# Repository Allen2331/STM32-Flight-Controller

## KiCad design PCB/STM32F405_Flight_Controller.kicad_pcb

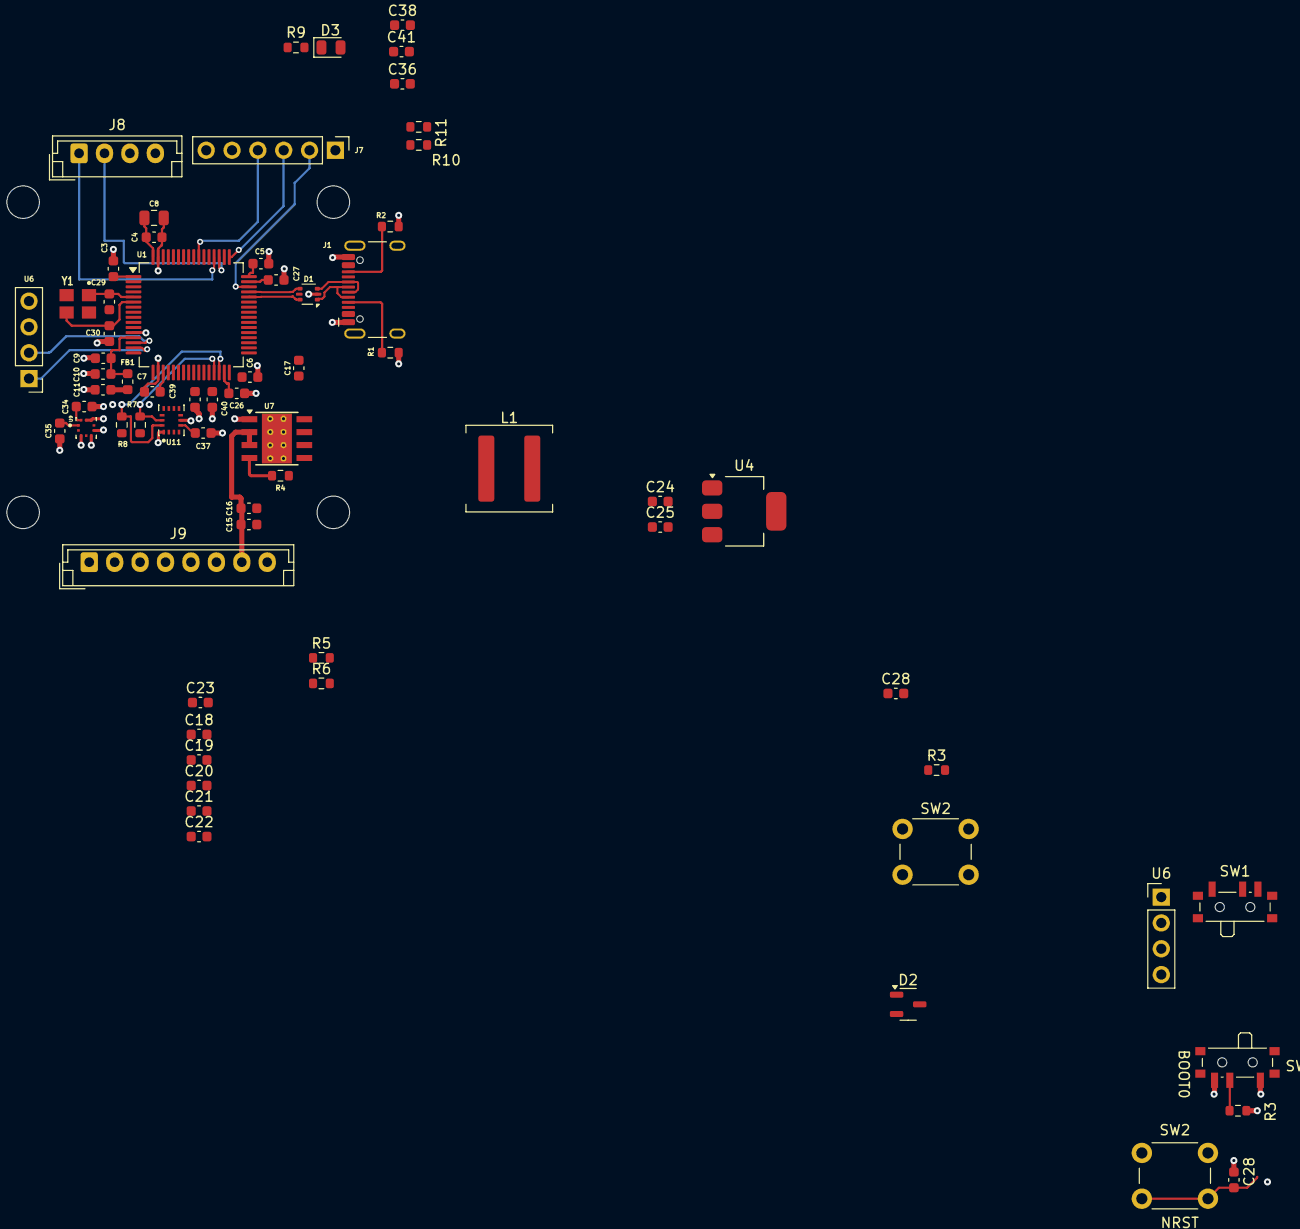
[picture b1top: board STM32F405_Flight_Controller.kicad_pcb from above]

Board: 4 copper layers, 71 parts (0 on the bottom side), 39 nets.

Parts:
C3, C4, C5, C6, C7, C18, C28, C28#2, C34, C35, C38, C41: 100nF; C_0603_1608Metric
C8: 10uF; C_0805_2012Metric
C9, C37: 10nF; C_0603_1608Metric
C10, C11, C17, C36: 1uF; C_0603_1608Metric
C15: 10uF; C_0603_1608Metric
C16: 220nF; C_0603_1608Metric
C19: 39pF; C_0603_1608Metric
C20, C21, C22, C23: 22uF; C_0603_1608Metric
C24, C25: 4.7uF; C_0603_1608Metric
C26, C27: 2.2uF; C_0603_1608Metric
C29, C30: 15pF; C_0603_1608Metric
C39: 0.1u; C_0603_1608Metric
C40: 2.2u; C_0603_1608Metric
D1: USBLC6-2P6; SOT-666
D2: BAT54C; SOT-23-3
D3: LED; LED_0805_2012Metric
FB1: FerriteBead; L_0603_1608Metric
H1, H2, H3, H4: MountingHole; MountingHole_3.2mm_M3_ISO7380
J1: USB_C_Receptacle_USB2.0_16P; USB_C_Receptacle_HCTL_HC-TYPE-C-16P-01A
J7: SWD; PinHeader_1x06_P2.54mm_Vertical
J8: Conn_01x04; JST_EH_B4B-EH-A_1x04_P2.50mm_Vertical
J9: Conn_01x08; JST_EH_B8B-EH-A_1x08_P2.50mm_Vertical
L1: 6.8uH; L_Coilcraft_XAL7030-682
R1, R2: 5.1K; R_0603_1608Metric
R3, R3#2, R11: 10K; R_0603_1608Metric
R4, R5: 100k; R_0603_1608Metric
R6: 24.9k; R_0603_1608Metric
R7, R8: 2.2K; R_0603_1608Metric
R9: 1K; R_0603_1608Metric
R10: 15K; R_0603_1608Metric
SW1, SW1#2: SW_SPDT; SW_SPDT_PCM12
SW2, SW2#2: SW_Push; SW_PUSH_6mm_H4.3mm
U1: STM32F405RGTx; LQFP-64_10x10mm_P0.5mm
U4: AP7361C-33E; SOT-223-3_TabPin2
U6, U6#2: PinHeader_1x04_P2.54mm_Vertical
U7: LMR33640DDDA; Texas_HSOP-8-1EP_3.9x4.9mm_P1.27mm_ThermalVias
U9: BMP390L
U11: XDCR_ICM-42670-P
Y1: 16MHz Crystal; OSC_X322516MLB4SI

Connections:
+3.3V: C3.1, C4.1, C5.1, C6.1, C7.1, C8.1, C11.1, C25.2, C34.1, C35.1, C36.1, C37.2, C38.1, C39.1, C40.1, D3.2 (A), FB1.1, J7.1, J8.3, R7.1, R8.1, SW1.1 (A), SW1#2.1 (A), U1.1 (VBAT), U1.19 (VDD), U1.32 (VDD), U1.48 (VDD), U1.64 (VDD), U4.3 (VO), U9.1 (VDDIO), U9.10 (VDD), U11.5 (VDDIO), U11.8 (VDD), U11.12 (CS)
+5V: C19.2, C20.2, C21.2, C22.2, C23.2, C24.2, D2.2 (A1), D2.3 (K), L1.2, R5.1, U4.1 (VI), U6.3 (5V), U6#2.3 (5V)
+BATT: C15.1, C16.1, J9.7, R10.1, U7.2 (VIN), U7.3 (EN)
BATT_SENSE: R10.2, R11.1, U1.9 (PC1)
BMP_INT: U1.61 (PB8), U9.7 (INT)
BOOT0: R3.2, R3#2.2, SW1.2 (B), SW1#2.2 (B), U1.60 (BOOT0)
ESC_1: J9.6, U1.26 (PB0)
ESC_2: J9.5, U1.27 (PB1)
ESC_3: J9.4, U1.38 (PC7)
ESC_4: J9.3, U1.37 (PC6)
GND: C3.2, C4.2, C5.2, C6.2, C7.2, C8.2, C9.2, C10.2, C11.2, C15.2, C16.2, C17.2, C20.1, C21.1, C22.1, C23.1, C24.1, C25.1, C26.2, C27.2, C28.1, C28#2.1, C29.1, C30.1, C34.2, C35.2, C36.2, C37.1, C38.2, C39.2, C40.2, C41.2, D1.2 (VN), J1.A1 (GND), J1.A12 (GND), J1.B1 (GND), J1.B12 (GND), J1.S1 (SHIELD), J7.6, J8.4, J9.8, R1.2, R2.2, R3.1, R3#2.1, R6.2, R9.1, R11.2, SW1.3 (C), SW1#2.3 (C), SW2.1, SW2#2.1, U1.12 (VSSA), U1.18 (VSS), U1.63 (VSS), U4.2 (GND), U6.4 (GND), U6#2.4 (GND), U7.1 (GND), U7.9 (GND), U9.3 (VSS), U9.5 (SDO), U9.6 (CSB), U9.8 (VSS), U9.9 (VSS), U11.1 (SDO), U11.6 (GND), Y1.2, Y1.4
IMU_INT: U1.33 (PB12), U11.4 (INT)
NRST: C28.2, C28#2.2, J7.5, SW2.2, SW2#2.2, U1.7 (NRST)
unnamed: D1.5 (VP), D2.1 (A2), J1.A4 (VBUS), J1.A9 (VBUS), J1.B4 (VBUS), J1.B9 (VBUS)
unnamed: D3.1 (K), R9.2
unnamed: J1.A5 (CC1), R1.1
unnamed: J1.B5 (CC2), R2.1
unnamed: C29.2, U1.5 (PH0), Y1.1
unnamed: C30.2, U1.6 (PH1), Y1.3
unnamed: C26.1, U1.31 (VCAP_1)
unnamed: C27.1, U1.47 (VCAP_2)
unnamed: C9.1, C10.1, FB1.2, U1.13 (VDDA)
unnamed: C18.1, U7.7 (BOOT)
unnamed: C19.1, R5.2, R6.1, U7.5 (FB)
unnamed: R4.1, U7.4 (PG)
unnamed: C18.2, L1.1, U7.8 (SW)
unnamed: C17.1, R4.2, U7.6 (VCC)
SCL: R7.2, U1.29 (PB10), U9.2 (SCK), U11.13 (SCL)
SDA: R8.2, U1.30 (PB11), U9.4 (SDI), U11.14 (SDA)
SWCLK: J7.3, U1.49 (PA14)
SWDIO: J7.2, U1.46 (PA13)
SWO: J7.4, U1.55 (PB3)
UART1_RX: U1.15 (PA1), U6.1 (RX), U6#2.1 (RX)
UART1_TX: U1.14 (PA0), U6.2 (TX), U6#2.2 (TX)
UART2_RX: J8.1, U1.52 (PC11)
UART2_TX: J8.2, U1.51 (PC10)
UART_ESC: J9.1, U1.54 (PD2)
USB_C_D_N: D1.1 (L1), D1.6 (L1), J1.A7 (D-), J1.B7 (D-), U1.44 (PA11)
USB_C_D_P: D1.3 (L2), D1.4 (L2), J1.A6 (D+), J1.B6 (D+), U1.45 (PA12)

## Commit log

2024-08-29 Initial commit of STM32 Flight Controller
2024-09-09 Create Schematic Folder
2024-09-09 Create PDF
2024-09-19 Add files via upload
    Updated schematic
2024-09-19 Add files via upload
    Added PCB file
2024-09-20 Add files via upload
    PNG of layers
2024-09-27 Add files via upload
    updated
2024-09-27 Create a
2024-09-27 Add files via upload
    added gerbers
2024-09-30 Add files via upload
    updated layout
2024-10-01 firmware files
2024-10-01 updated folder name
2024-10-01 folder name
2024-10-01 name
2024-10-23 Add files via upload
    pdf version of schematic
2024-10-28 created MPU6050 header
2024-11-04 added mpu6050
2024-11-04 register address
2024-11-11 added to mpu6050 header
2024-11-21 bmp280
2025-03-03 Add files via upload
    Updated schematic with new sensors
2025-03-04 Add files via upload
    Added sheets
